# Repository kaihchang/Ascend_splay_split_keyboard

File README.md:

# Kai Ascend, a wireless split keyboard with encoders & displays

First time designing my own keyboard. Also my first Kicad project.

I wanted a board with both MX and Choc switches, creating a natural elevation when used without wrist rests. One of the reasons I start using split ergos is to save desk space, so I'd like my board to be wireless (utilizing ZMK) and not rely on extra supports.
Thought about getting rid of "Q" and "P" positions since I prefer using extra pinky column (same as pinky column in schema but anyway) for those, but then that doesn't really save any space and pin, so I kept them eventually.

PCB:

Build:

With tenting:

Some suggested to use wires instead of infills to make soldering easier but keep the infills for the environment cuz' manufacturers are gonna use them anyways, so I added those in v1.3 and had some minor changes.
Haven't edited the STL files for the case of v1.3.

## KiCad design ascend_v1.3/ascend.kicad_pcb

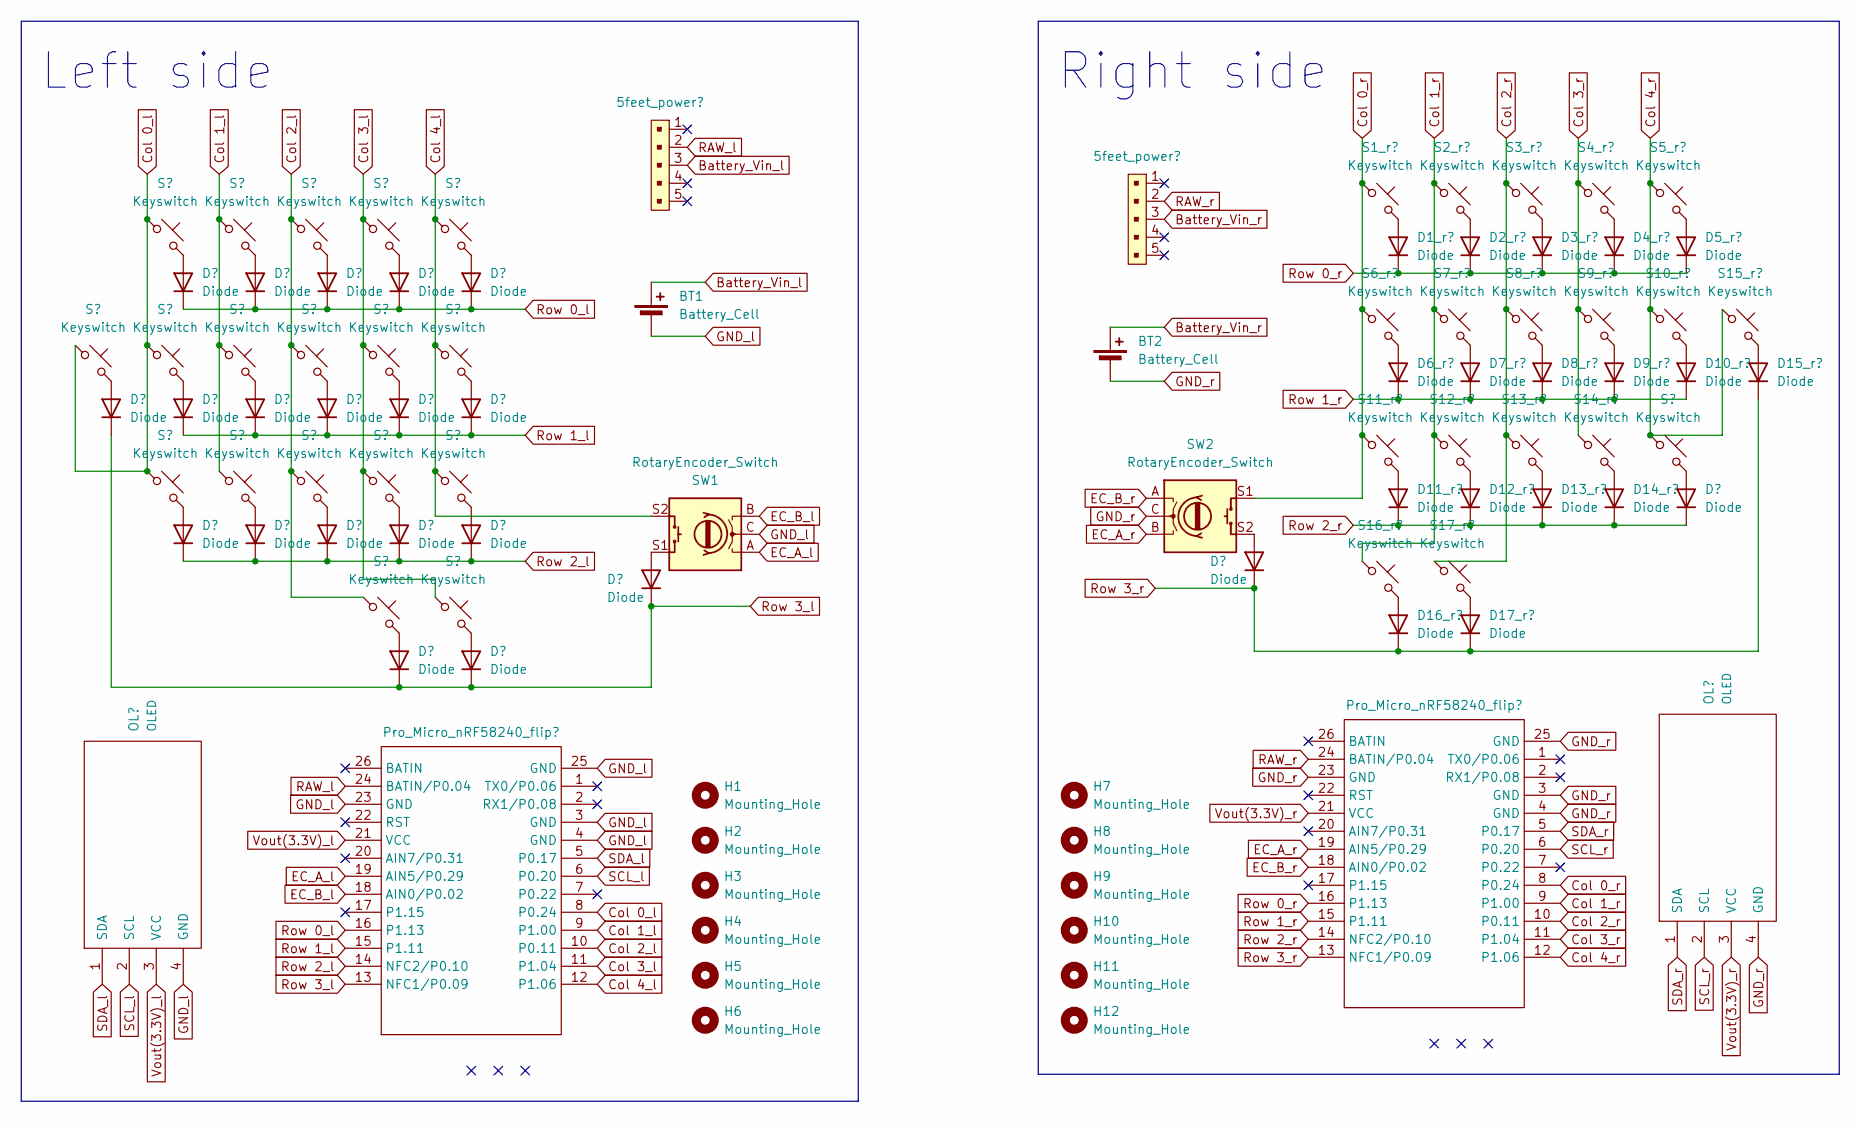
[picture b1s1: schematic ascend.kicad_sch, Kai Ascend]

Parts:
5feet_power1, 5feet_power2: B5B-XH-A_LF__SN_; Switch_slide_TH_5P; MPN B5B-XH-A(LF)(SN); Digi-Key_PN 455-2270-ND
BT1, BT2: Battery_Cell; JST_XH_2.54mm_vertical
D1, D1_r1, D2, D2_r1, D3, D3_r1, D4, D4_r1, D5, D5_r1, D6, D6_r1, D7, D7_r1, D8, D8_r1, D9, D9_r1, D10, D10_r1, D11, D11_r1, D12, D12_r1, D13, D13_r1, D14, D14_r1, D15, D15_r1, D16, D16_r1, D17, D17_r1, D18, D18_r1, D19, D20: Diode; Compatible_diode_TH_SMD
H1, H2, H3, H4, H5, H6, H7, H8, H9, H10, H11, H12: Mounting_Hole; MountingHole_3.2mm_M3
OL1, OL2: OLED; OLED_v2
Pro_Micro_nRF58240_flip1, Pro_Micro_nRF58240_flip2: Pro Micro nRF52840
S1, S1_r1, S2, S2_r1, S3, S3_r1, S4, S5, S5_r1, S6, S6_r1, S7, S7_r1, S8, S9, S9_r1, S10, S10_r1, S11, S11_r1, S12, S12_r1, S13, S13_r1, S14_r1, S15, S15_r1, S16, S16_r1, S17, S17_r1, S18_r1: Keyswitch; Hotswap_MX_Plated_1.00u
S4_r1, S8_r1, S14, S18: Keyswitch; Hotswap_Choc_V1_Plated_1.00u
SW1, SW2: RotaryEncoder_Switch; RotaryEncoder_Alps_EC12E-Switch_Vertical_H20mm

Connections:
Battery_Vin_l: 5feet_power1.3, BT1.1 (+)
Battery_Vin_r: 5feet_power2.3, BT2.1 (+)
Col 0_l: Pro_Micro_nRF58240_flip1.8 (P0.24), S1.1, S2.1, S3.1, S4.1
Col 0_r: Pro_Micro_nRF58240_flip2.8 (P0.24), S1_r1.1, S2_r1.1, S3_r1.1, SW2.S1
Col 1_l: Pro_Micro_nRF58240_flip1.9 (P1.00), S5.1, S6.1, S7.1
Col 1_r: Pro_Micro_nRF58240_flip2.9 (P1.00), S4_r1.1, S5_r1.1, S6_r1.1, S7_r1.1
Col 2_l: Pro_Micro_nRF58240_flip1.10 (P0.11), S8.1, S9.1, S10.1, S14.1
Col 2_r: Pro_Micro_nRF58240_flip2.10 (P0.11), S8_r1.1, S9_r1.1, S10_r1.1, S11_r1.1
Col 3_l: Pro_Micro_nRF58240_flip1.11 (P1.04), S11.1, S12.1, S13.1, S18.1
Col 3_r: Pro_Micro_nRF58240_flip2.11 (P1.04), S12_r1.1, S13_r1.1, S14_r1.1
Col 4_l: Pro_Micro_nRF58240_flip1.12 (P1.06), S15.1, S16.1, S17.1, SW1.S2
Col 4_r: Pro_Micro_nRF58240_flip2.12 (P1.06), S15_r1.1, S16_r1.1, S17_r1.1, S18_r1.1
EC_A_l: Pro_Micro_nRF58240_flip1.19 (AIN5/P0.29), SW1.A
EC_A_r: Pro_Micro_nRF58240_flip2.19 (AIN5/P0.29), SW2.B
EC_B_l: Pro_Micro_nRF58240_flip1.18 (AIN0/P0.02), SW1.B
EC_B_r: Pro_Micro_nRF58240_flip2.18 (AIN0/P0.02), SW2.A
GND_l: BT1.2 (-), OL1.4 (GND), Pro_Micro_nRF58240_flip1.3 (GND), Pro_Micro_nRF58240_flip1.4 (GND), Pro_Micro_nRF58240_flip1.23 (GND), Pro_Micro_nRF58240_flip1.25 (GND), SW1.C
GND_r: BT2.2 (-), OL2.4 (GND), Pro_Micro_nRF58240_flip2.3 (GND), Pro_Micro_nRF58240_flip2.4 (GND), Pro_Micro_nRF58240_flip2.23 (GND), Pro_Micro_nRF58240_flip2.25 (GND), SW2.C
unnamed: D1.2 (A), S1.2
unnamed: D1_r1.2 (A), S1_r1.2
unnamed: D2.2 (A), S2.2
unnamed: D2_r1.2 (A), S2_r1.2
unnamed: D3.2 (A), S3.2
unnamed: D3_r1.2 (A), S3_r1.2
unnamed: D4.2 (A), S4.2
unnamed: D4_r1.2 (A), S4_r1.2
unnamed: D5.2 (A), S5.2
unnamed: D5_r1.2 (A), S5_r1.2
unnamed: D6.2 (A), S6.2
unnamed: D6_r1.2 (A), S6_r1.2
unnamed: D7.2 (A), S7.2
unnamed: D7_r1.2 (A), S7_r1.2
unnamed: D8.2 (A), S8.2
unnamed: D8_r1.2 (A), S8_r1.2
unnamed: D9.2 (A), S9.2
unnamed: D9_r1.2 (A), S9_r1.2
unnamed: D10.2 (A), S10.2
unnamed: D10_r1.2 (A), S10_r1.2
unnamed: D11.2 (A), S11.2
unnamed: D11_r1.2 (A), S11_r1.2
unnamed: D12.2 (A), S12.2
unnamed: D12_r1.2 (A), S12_r1.2
unnamed: D13.2 (A), S13.2
unnamed: D13_r1.2 (A), S13_r1.2
unnamed: D14.2 (A), S14.2
unnamed: D14_r1.2 (A), S14_r1.2
unnamed: D15.2 (A), S15.2
unnamed: D15_r1.2 (A), S15_r1.2
unnamed: D16.2 (A), S16.2
unnamed: D16_r1.2 (A), S16_r1.2
unnamed: D17.2 (A), S17.2
unnamed: D17_r1.2 (A), S17_r1.2
unnamed: D18.2 (A), S18.2
unnamed: D18_r1.2 (A), S18_r1.2
unnamed: D19.2 (A), SW1.S1
unnamed: D20.2 (A), SW2.S2
RAW_l: 5feet_power1.2, Pro_Micro_nRF58240_flip1.24 (BATIN/P0.04)
RAW_r: 5feet_power2.2, Pro_Micro_nRF58240_flip2.24 (BATIN/P0.04)
Row 0_l: D2.1 (K), D5.1 (K), D8.1 (K), D11.1 (K), D15.1 (K), Pro_Micro_nRF58240_flip1.16 (P1.13)
Row 0_r: D1_r1.1 (K), D5_r1.1 (K), D9_r1.1 (K), D12_r1.1 (K), D15_r1.1 (K), Pro_Micro_nRF58240_flip2.16 (P1.13)
Row 1_l: D3.1 (K), D6.1 (K), D9.1 (K), D12.1 (K), D16.1 (K), Pro_Micro_nRF58240_flip1.15 (P1.11)
Row 1_r: D2_r1.1 (K), D6_r1.1 (K), D10_r1.1 (K), D13_r1.1 (K), D16_r1.1 (K), Pro_Micro_nRF58240_flip2.15 (P1.11)
Row 2_l: D4.1 (K), D7.1 (K), D10.1 (K), D13.1 (K), D17.1 (K), Pro_Micro_nRF58240_flip1.14 (NFC2/P0.10)
Row 2_r: D3_r1.1 (K), D7_r1.1 (K), D11_r1.1 (K), D14_r1.1 (K), D17_r1.1 (K), Pro_Micro_nRF58240_flip2.14 (NFC2/P0.10)
Row 3_l: D1.1 (K), D14.1 (K), D18.1 (K), D19.1 (K), Pro_Micro_nRF58240_flip1.13 (NFC1/P0.09)
Row 3_r: D4_r1.1 (K), D8_r1.1 (K), D18_r1.1 (K), D20.1 (K), Pro_Micro_nRF58240_flip2.13 (NFC1/P0.09)
SCL_l: OL1.2 (SCL), Pro_Micro_nRF58240_flip1.6 (P0.20)
SCL_r: OL2.2 (SCL), Pro_Micro_nRF58240_flip2.6 (P0.20)
SDA_l: OL1.1 (SDA), Pro_Micro_nRF58240_flip1.5 (P0.17)
SDA_r: OL2.1 (SDA), Pro_Micro_nRF58240_flip2.5 (P0.17)
Vout(3.3V)_l: OL1.3 (VCC), Pro_Micro_nRF58240_flip1.21 (VCC)
Vout(3.3V)_r: OL2.3 (VCC), Pro_Micro_nRF58240_flip2.21 (VCC)

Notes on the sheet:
Left side
Right side

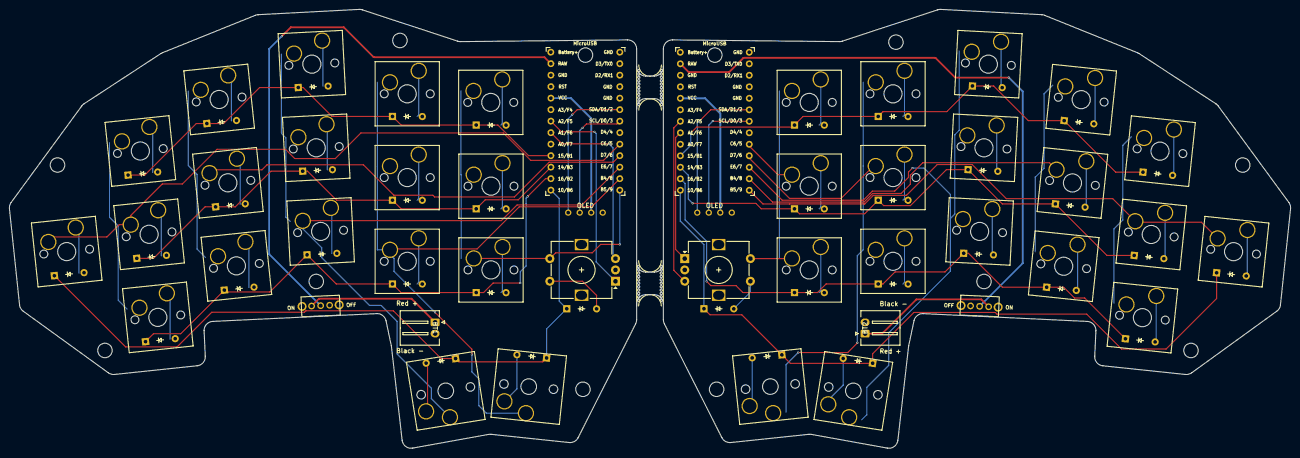
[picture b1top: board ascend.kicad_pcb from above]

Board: 2 copper layers, 283.0 x 96.9 mm, 98 parts (0 on the bottom side), 72 nets.

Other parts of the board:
mouse-bite-5mm-slot, mouse-bite-5mm-slot#2: VAL**; mouse-bite-5mm-slot

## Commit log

2024-03-01 user update
2024-03-12 local change
2024-03-12 readme update
2024-04-09 user update v1.3
2024-04-10 add step file
2024-04-10 update v1.3 case step file
2024-06-25 update case
